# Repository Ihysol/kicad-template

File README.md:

# KiCAD Project Template

<!-- Keep this line! Rendered picture of PCB will be displayed after production files are pushed to branch -->

This template provides a clean KiCad repository structure for embedded hardware projects.

---

## Features

Clean structure for hardware development with automated component import and library management.

**DISCLAIMER:** KiCad files are difficult to edit simultaneously. Limit active work on project files to one person at a time; other tasks like research or tests can be done in parallel.

---

## Getting Started

1. **Clone the repository:**

```bash
git clone https://github.com/Ihysol/kicad-template.git
```

2. **Set up your KiCad project:**

* Add symbols, footprints, and 3D models in `Lib-*` folders
* Check for existing footprints online (ComponentSearchEngine, Mouser, Digi-Key)
* Add parts manually or via your preferred library management workflow
* Keep all other libraries local; do not use global libraries

3. **Update this README** to describe your project

---

## Ordering Your PCB

* Use Git tags for PCBs sent to production to snapshot the PCB at that moment
* Use the [KiCAD BOM Mouser Order Script](https://github.com/Ihysol/KiCAD_BOM_Mouser_Order_Script) to generate a BOM cart automatically

---

## Folder Structure

* **Hardware/**: KiCad files, symbols, footprints, and 3D models. Add custom footprints here
* **Production/**: Final Gerber files for PCB ordering
* **Docs/**: Documentation, notes, and changelogs. Link datasheets externally and update after production

---

## Version Control

* Use the main branch for the current hardware version
* Tag commits corresponding to production-ready PCBs (e.g., `v1.0`)
* Keep each repository dedicated to a single hardware design
* Use separate repositories for multiple PCB projects

---

## Best Practices

* Always include local libraries in the repository; avoid using global KiCad libraries
* Use tags to reference production-ready hardware versions
* Limit simultaneous editing on KiCad files to **one person** at a time

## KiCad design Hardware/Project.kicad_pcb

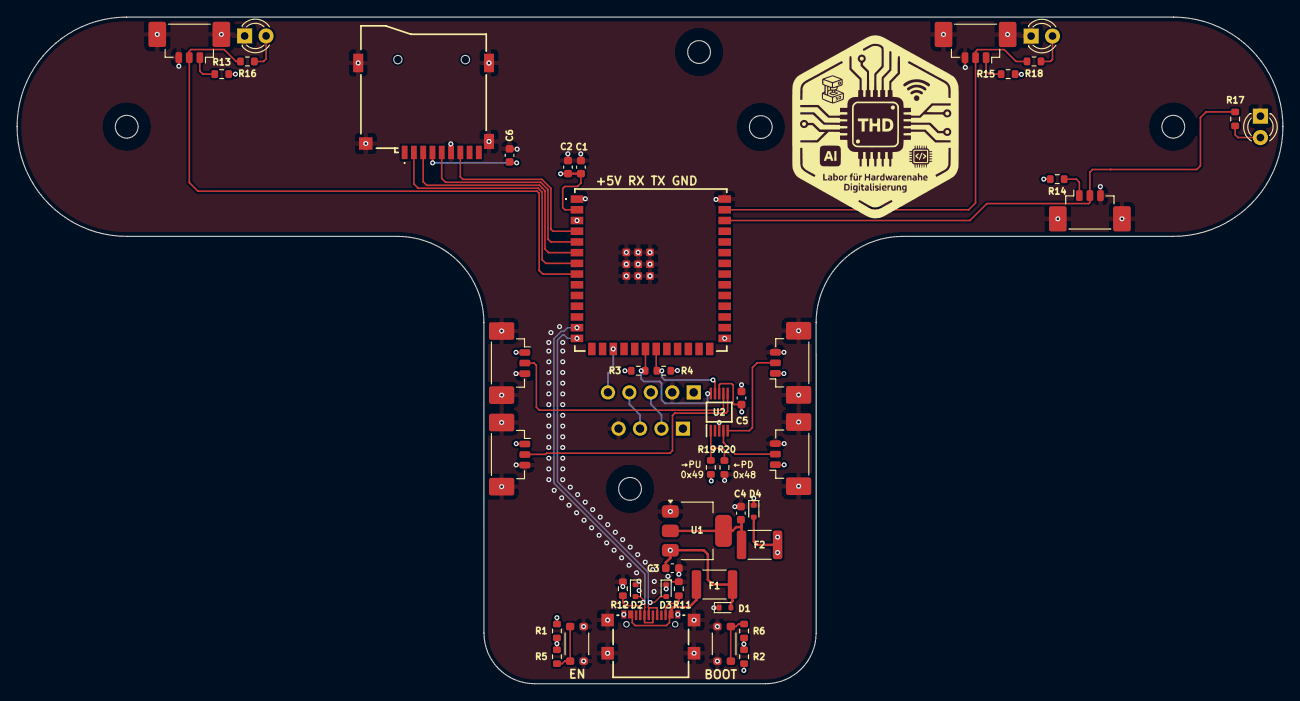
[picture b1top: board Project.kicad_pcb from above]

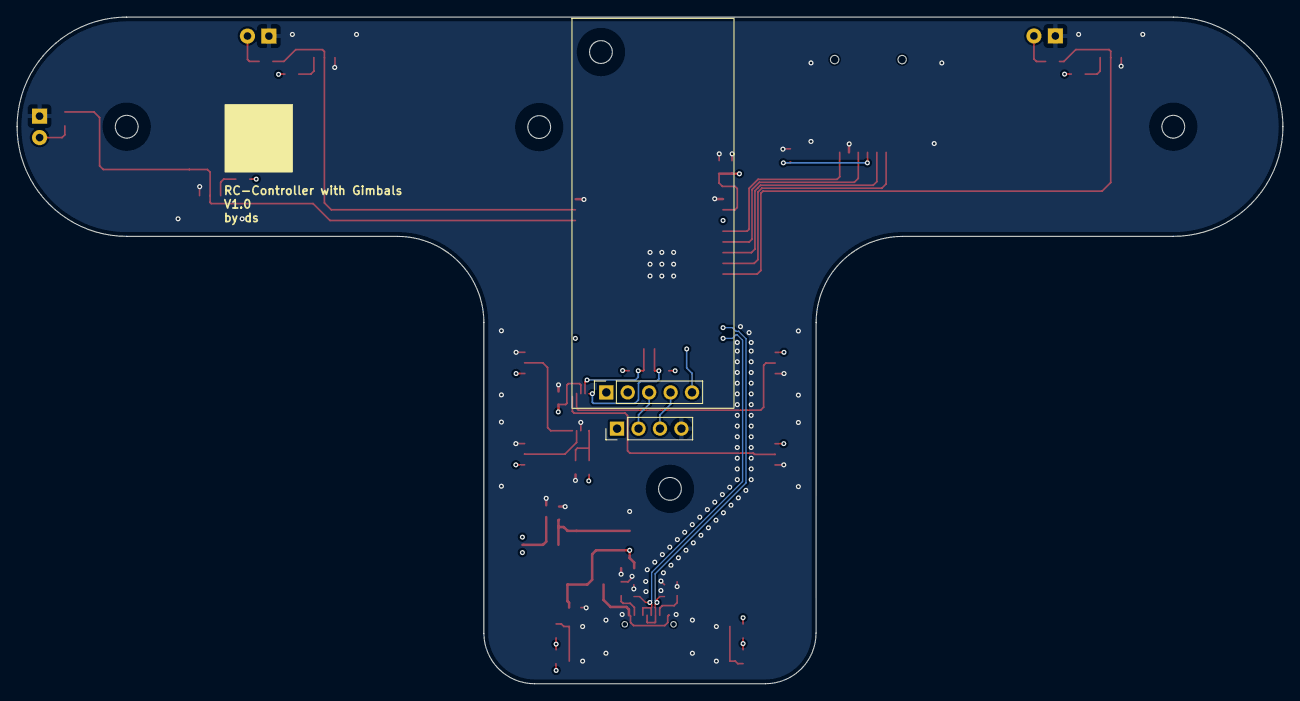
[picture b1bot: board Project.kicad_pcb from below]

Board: 4 copper layers, 150.0 x 79.0 mm, 51 parts (2 on the bottom side), 36 nets.

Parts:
C1, C5, C6: 100n; C_0603_1608Metric
C2: 22u; C_0603_1608Metric
C3, C4: 1uF; C_0603_1608Metric
D1, D2, D3, D4: ESD5Zxx; D_SOD-523
D5: LED_Blue; LED_D3.0mm
D6, D7: LED_Red; LED_D3.0mm
F1, F2: Fuse_1812; Fuse_1812_4532Metric
H1, H2, H3, H4: MountingHole; MountingHole_2.7mm_M2.5
IC1: ESP32-S3-WROOM-1U-N16
J1, J2, J3, J4, J6, J7, J8: JST_MOLEX-1.25-3P; Molex_PicoBlade_53398-0371_1x03-1MP_P1.25mm_Vertical
J5: USB_C_2.0
J9: TTL_Header; PinHeader_1x04_P2.54mm_Vertical
J10: Transceiver_Socket; SX1280_Transceiver
J11: Micro_SD_Card; MSD1A
R1, R2: 12k; R_0603_1608Metric
R3, R4: 2k2; R_0603_1608Metric
R5, R6: 470R; R_0603_1608Metric
R11, R12: 5k1; R_0603_1608Metric
R13, R14, R15, R19, R20: 10k; R_0603_1608Metric
R16, R17, R18: 120R; R_0603_1608Metric
SW1, SW2: KMR421NGLFS
U1: TLV1117LV33DCYR; SOT-223-3_TabPin2
U2: ADS1015IDGSR

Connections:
+3V3: C1.1, C2.1, C5.1, C6.1, D4.2 (A2), F2.1, IC1.2 (3V3), J1.1, J2.1, J3.1, J4.1, J11.4 (VDD), R1.2, R2.2, R3.1, R4.1, R13.2, R14.2, R15.2, R19.1, U2.8 (VDD)
+5V: C3.1, D1.2 (A2), F1.1, J9.1, J10.1, U1.3 (VI)
/ADS1015/AIO0: J2.2, U2.4 (AIN0)
/ADS1015/AIO1: J1.2, U2.5 (AIN1)
/ADS1015/AIO2: J3.2, U2.7 (AIN3)
/ADS1015/AIO3: J4.2, U2.6 (AIN2)
/ADS1015/SCL: IC1.20 (IO12), R3.2, U2.10 (SCL)
/ADS1015/SDA: IC1.21 (IO13), R4.2, U2.9 (SDA)
/ELRS_Transceiver/SPORT: IC1.17 (IO9), J10.5
/ESP32/IO_Arm: IC1.39 (IO1), J8.2, R18.2
/ESP32/IO_Failsafe: IC1.38 (IO2), J7.2, R17.2
/ESP32/IO_Man_Auto_Mode: IC1.8 (IO15), J6.2, R16.2
/ESP32/SD_CLK: IC1.5 (IO5), J11.5 (CLK)
/ESP32/SD_CS: IC1.7 (IO7), J11.2 (DAT3/CD)
/ESP32/SD_MISO: IC1.4 (IO4), J11.7 (DAT0)
/ESP32/SD_MOSI: IC1.6 (IO6), J11.3 (CMD)
/ESP32/USB_N: D2.2 (A2), IC1.13 (IO19/USB_D-), J5.A7 (D-), J5.B7 (D-)
/ESP32/USB_P: D3.2 (A2), IC1.14 (IO20/USB_D+), J5.A6 (D+), J5.B6 (D+)
BOOT0: IC1.27 (IO0), R2.1, R6.2
ESP_EN: IC1.3 (EN), R1.1, R5.2
GND: C1.2, C2.2, C3.2, C4.2, C5.2, C6.2, D1.1 (A1), D2.1 (A1), D3.1 (A1), D4.1 (A1), D5.1 (K), D6.1 (K), D7.1 (K), IC1.1 (GND_1), IC1.40 (GND_2), IC1.41 (GND_3), IC1.42 (GND_4), IC1.43 (GND_5), IC1.44 (GND_6), IC1.45 (GND_7), IC1.46 (GND_8), IC1.47 (GND_9), IC1.48 (GND_10), IC1.49 (GND_11), J1.3, J1.MP (Pin_4), J2.3, J2.MP (Pin_4), J3.3, J3.MP (Pin_4), J4.3, J4.MP (Pin_4), J5.A1 (GND), J5.A12 (GND), J5.S1 (SHIELD), J6.3, J6.MP (Pin_4), J7.3, J7.MP (Pin_4), J8.3, J8.MP (Pin_4), J9.4, J10.2, J11.6 (VSS), J11.9 (SHIELD), R11.2, R12.2, R20.2, SW1.2 (B), SW2.2 (B), U1.1 (GND), U2.3 (GND)
unnamed: D5.2 (A), R16.1
unnamed: D6.2 (A), R17.1
unnamed: D7.2 (A), R18.1
unnamed: F1.2, J5.A4 (VBUS), J5.A9 (VBUS)
unnamed: J5.A5 (CC1), R12.1
unnamed: J5.B5 (CC2), R11.1
unnamed: J6.1, R13.1
unnamed: J7.1, R14.1
unnamed: J8.1, R15.1
unnamed: R5.1, SW1.1 (A)
unnamed: R6.1, SW2.1 (A)
unnamed: C4.1, F2.2, U1.2 (VO)
unnamed: R19.2, R20.1, U2.1 (ADDR)
RX: J9.2, J10.3
TX: J9.3, J10.4

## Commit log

2025-07-25 kicad-ci.yml
2025-07-25 Rename blank.yml to kicad-ci.yml
2025-10-08 added automation script
2025-10-08 code comment cleaning
2025-10-08 swap to sexpdata implementation from regex to parse data (fixes regex parsing bug where no or only first part was appended)
2025-10-08 finalized gui functionality and bugfixing
2025-10-08 modified gui to also work when bundled into exe using pyinstaller
2025-10-08 added ADD_CSE_ZIPs_HERE.txt
2025-10-08 updated folder structure and prebuilt .exe (windows only atm)
2025-10-08 added prebuilt gui_app (linux)
2025-10-09 added custom font (NotoSans-Regular.ttf) and added autodiscover for the needed files/folders
2025-10-09 moved production folder for cleaner folder structure
2025-10-09 project housekeeping + moved and modified .gitignore to ignore zips from cse_manager + renamed scripts to cse_manager (since it only houses this script)
2025-10-09 Added MIT LICENSE as well as updated README.md and added a Hardware/cse_manager/README.md
2025-10-09 re-added footprint path config for kicad_pro-file
2025-10-09 Update .gitlab-ci.yml
    updated .gitlab-cli.yaml to match new destination of Production folder
2025-10-13 experimental file renaming
2025-10-13 renaming feature
2025-10-13 added configmanager.py
2025-10-13 renaming feature + auto font search + config for presistant tickbox state + updated purge and import code depending on checkbox + font will now be searched in same folder or below (previously static 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
2025-10-13 cosmetic fix for hyperlink footer
2025-10-13 re-implemented persistant checkbox feature
2025-10-13 code formatting
2025-10-13 removed env
2025-10-17 Folder structure update and dru_manager script + moved scripts into Hardware/scripts folder + added dru_manager (applies correct dru_templates from .kicad_pcb layercount)
2025-10-17 added dru_manager.exe
2025-10-20 changed template to be conform with default kicad folder structure names
2025-10-22 export functionality
2025-10-22 advanced export feature implemented and tested
2025-10-22 re-implemented select/deselect all checkboxes and naming-override checkbox
2025-10-22 added dru_manager.py that automatically updates layer count and applies the correct dru file.
2025-10-22 fixed buttons not working when gui-size fix is applied
2025-10-22 merged DRC updater into the gui
2025-10-22 added lookup for correct 3dmodel-filename from footprint field
2025-10-23 fixed wrong 3d file import (old Lib-3d-files folder instead of 3dmodels)
2025-10-23 removed dru_manager.py
2025-10-23 removed the "_export" suffix for cleaner re-import procedure
2025-10-23 fixed export function, so that re-import with gui is now possible
2025-10-23 refactoring
2025-10-23 built klm.exe
2025-10-24 experimental: convert into correct kicad version while importing (kicad9 scheme <-> kicad 8 scheme)
2025-10-24 working symbol import in both kicad 9 and 8, 8 still got footprint issues
2025-10-27 working kicad 9 -> kicad 8 conversion
2025-10-27 code cleaning + added up-to-date DRU files
2025-10-27 code refactoring + split of gui into * gui_core.py (functions, interactions) * gui_ui.py (gui structure) * main_gui.py (entrypoint) + refactored cli_main.py + refactored library_manager.py + renamed 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
2025-10-27 refactoring + bugfix
2025-10-30 added executables + font fix
2025-11-05 added version
2025-11-05 cleaned project libraries from prior testing
2025-11-05 preperation for plugin conversion
2025-11-05 made zip-code case-insensitive
2025-11-05 testing
2025-11-05 added optional 2nd gui_wx.py
2025-11-05 added wxPython gui core functionality and styling
2025-11-05 wxPython gui port (move logic to backend)
2025-11-05 added all functionality to new wxPython gui
2025-11-06 port to new ui
2025-11-06 fixed logging as .exe + built exe
2025-11-06 added drag & drop feature + delete feature from list
2025-11-10 kicad_library_manager V1.0 release + Added delete function for project symbols in the export tab + Added more distinct visuals for status display + Added scan if symbol/footprints are missing in zip 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
2025-11-12 v1.0a (implemented import of footprints for older kicad versions)
2025-12-03 Added functionality to create mouser cart and submit it
2025-12-15 incorporated fork from: https://github.com/Darexsh/kicad-template
2025-12-15 added icons to everything. yes everything
2025-12-16 switched from numpy to csv parsing to minimize size of exe that is generated using pyinstaller
2025-12-16 changed to only import neccessary fields from parts as well as improoved startup time
2025-12-16 version 1.1 + implemented BOM generation from within the gui + improoved startup time + added log visibility checkbox * modified layout of tabs * moved open zip folder in the correct tab + added a op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
2025-12-18 library manager v1.1
2026-01-13 added documentation template
2026-01-13 removed trash
2026-01-19 added picture preview generation in gui
2026-01-19 moved to multiprocessed
2026-01-19 V1.2 release
    * image generation from pcb files
    + auto border detection for cropping generated images as well as custom border placement and settings
    + moved all gui tasks into subprocesses to not interrupt user experience
    * updated all table views to use DataViewListCtrl in zip, part export and mouser tab to steamline experience
    * BOM Generator: will now default to MNR or the first found column if there is no MNR
2026-01-20 mouser auto fix
2026-01-20 v1.2a hotfix
    * mouser auto order update
    * added progress bars to image rendering
2026-01-20 v1.2a hotfix
2026-01-20 removed kicad-ci.yml
2026-01-29 removed kicad-library-manager, since it was split into https://github.com/Ihysol/kicad-library-manager
2026-04-28 kicad 10 update to keep folders after crashes. Moved data for libraries one folder level up
2026-04-28 updated template
